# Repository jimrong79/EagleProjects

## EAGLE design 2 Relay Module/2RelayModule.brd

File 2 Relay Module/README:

2 Relay Module Using 2 G6D-1A-ASI-DC5 relay. Could be controlled by Arduino. Each output can output up to 4 Amps.

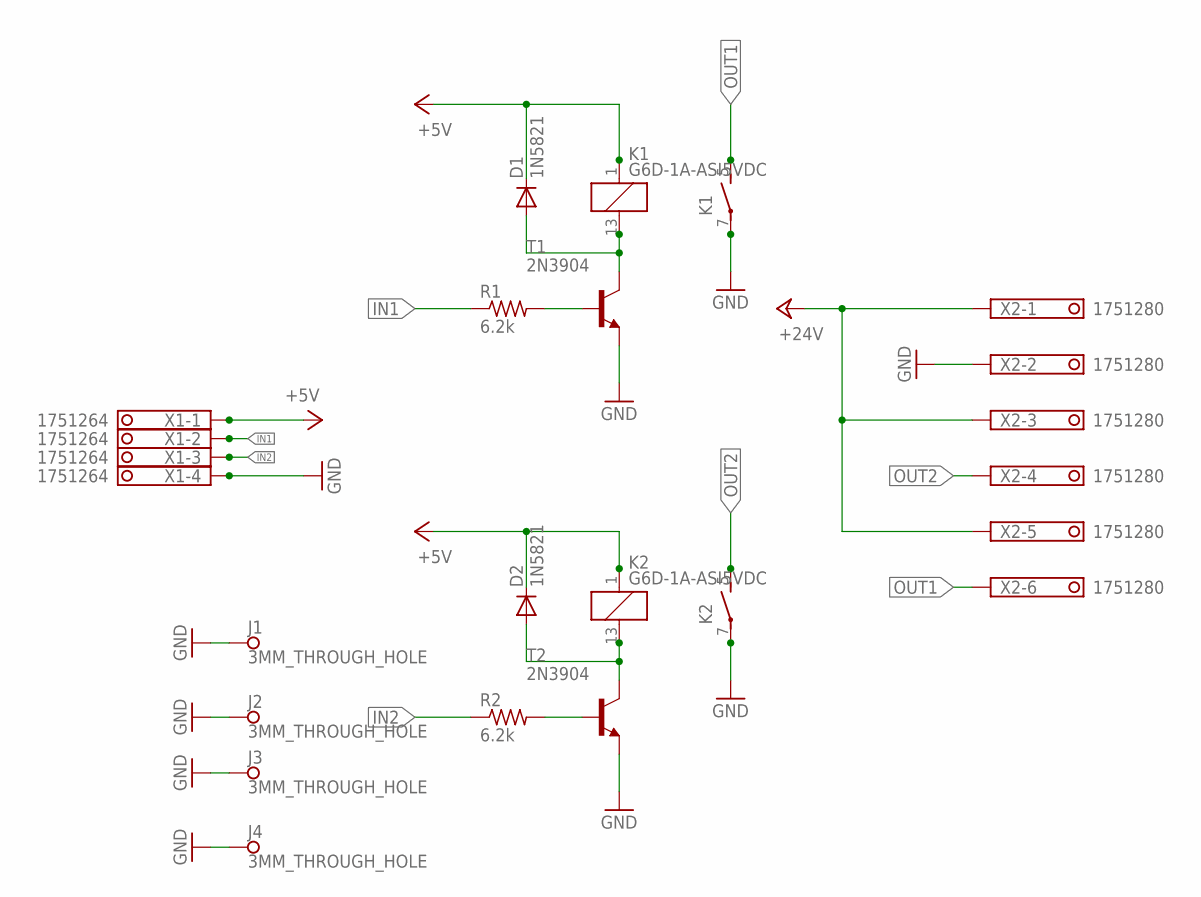
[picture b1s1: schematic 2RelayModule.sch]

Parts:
D1, D2: 1N5821; DO41-10
J1, J2, J3, J4: 3MM_THROUGH_HOLE
K1, K2: G6D-1A-ASI5VDC; G6D
R1, R2: 6.2k; 0207/10
T1, T2: 2N3904; TO92
X1: 1751264
X2: 1751280

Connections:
+5V: D1.C, D2.C, K1.1, K2.1, X1.1
+24V: X2.1, X2.3, X2.5
GND: J1.HOLE, J2.HOLE, J3.HOLE, J4.HOLE, K1.7, K2.7, T1.3 (E), T2.3 (E), X1.4, X2.2
IN1: R1.1, X1.2
IN2: R2.1, X1.3
unnamed: R1.2, T1.2 (B)
unnamed: R2.2, T2.2 (B)
unnamed: D1.A, K1.13 (2), T1.1 (C)
unnamed: D2.A, K2.13 (2), T2.1 (C)
OUT1: K1.5 (S), X2.6
OUT2: K2.5 (S), X2.4

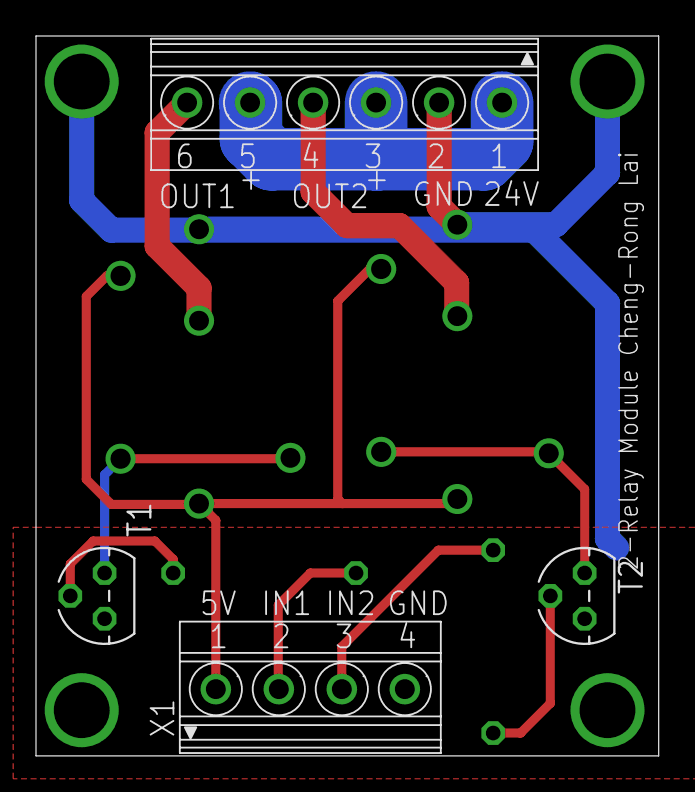
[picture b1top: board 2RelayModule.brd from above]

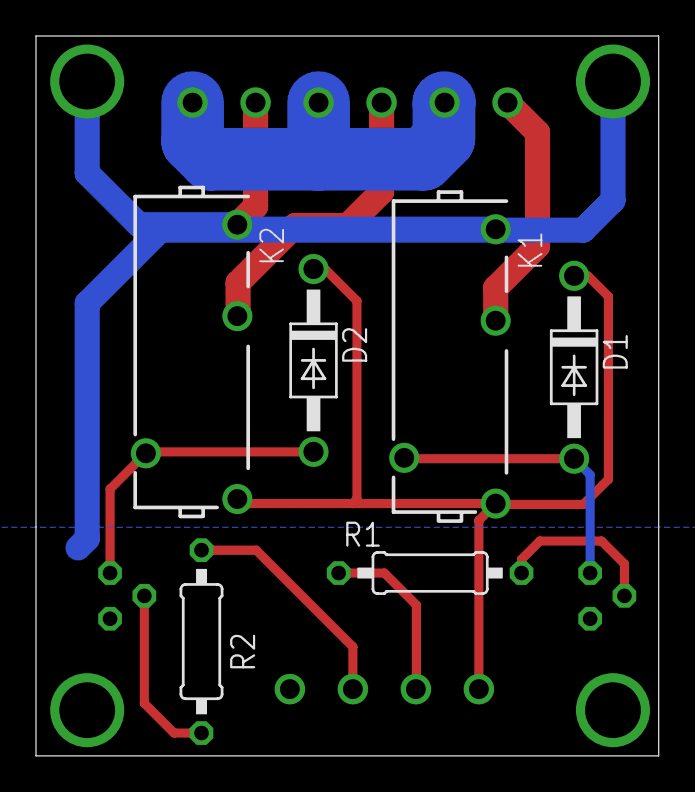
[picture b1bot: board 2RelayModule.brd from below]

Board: 2 copper layers, 34.6 x 40.0 mm, 14 parts (6 on the bottom side), 11 nets.
